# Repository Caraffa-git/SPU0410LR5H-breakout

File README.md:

# SPU0410LR5H-breakout

Simple SPU0410LR5H breakout board with an amplifier and a high-pass filter.

The panelized version is sized 35x75 mm and contains 4 boards.

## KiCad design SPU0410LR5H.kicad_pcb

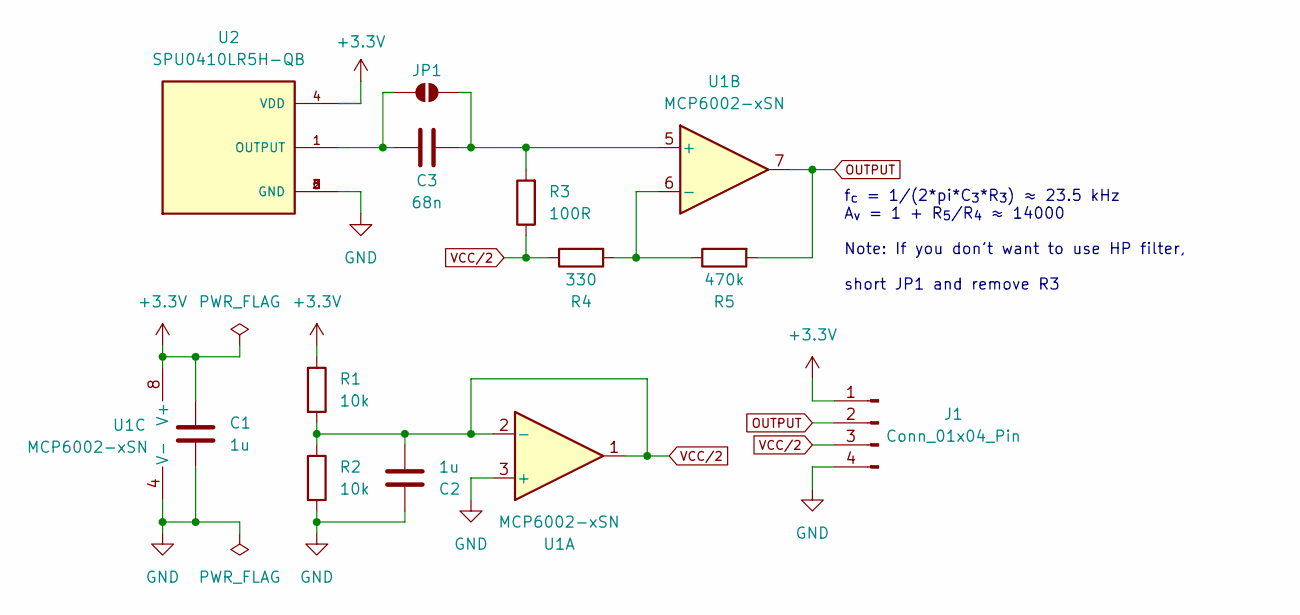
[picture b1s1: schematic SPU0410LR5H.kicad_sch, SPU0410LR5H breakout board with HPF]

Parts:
C1, C2: 1u; C_0805_2012Metric
C3: 68n; C_0805_2012Metric
J1: Conn_01x04_Pin; PinSocket_1x04_P2.54mm_Vertical
JP1: SolderJumper_2_Open; SolderJumper-2_P1.3mm_Open_RoundedPad1.0x1.5mm
R1, R2: 10k; R_0805_2012Metric
R3: 100R; R_0805_2012Metric
R4: 330; R_0805_2012Metric
R5: 470k; R_0805_2012Metric
U1: MCP6002-xSN; SOIC-8_3.9x4.9mm_P1.27mm
U2: SPU0410LR5H-QB; XDCR_SPU0410LR5H-QB; PARTREV H

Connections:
+3.3V: C1.1, J1.1, R1.1, U1.8 (V+), U2.4 (VDD)
GND: C1.2, C2.1, J1.4, R2.2, U1.3 (+), U1.4 (V-), U2.2 (GND), U2.3 (GND), U2.5 (GND), U2.6 (GND)
unnamed: C3.2, JP1.1 (A), U2.1 (OUTPUT)
unnamed: C3.1, JP1.2 (B), R3.2, U1.5 (+)
unnamed: R4.2, R5.1, U1.6 (-)
OUTPUT: J1.2, R5.2, U1.7
VCC/2: C2.2, J1.3, R1.2, R2.1, R3.1, R4.1, U1.1, U1.2 (-)

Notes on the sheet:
f_{c} = 1/(2*pi*C_{3}*R_{3}) ≈ 23.5 kHz A_{v} = 1 + R_{5}/R_{4} ≈ 14000 Note: If you don't want to use HP filter, short JP1 and remove R3

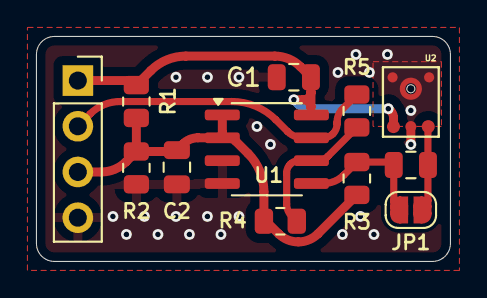
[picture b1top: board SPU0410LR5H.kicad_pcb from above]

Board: 2 copper layers, 23.0 x 12.5 mm, 16 parts (0 on the bottom side), 7 nets.

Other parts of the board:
kibuzzard-670AB1E7: G***; kibuzzard-670AB1E7
kibuzzard-670AB1F3: G***; kibuzzard-670AB1F3
kibuzzard-670AB20C: G***; kibuzzard-670AB20C
kibuzzard-670AB201: G***; kibuzzard-670AB201

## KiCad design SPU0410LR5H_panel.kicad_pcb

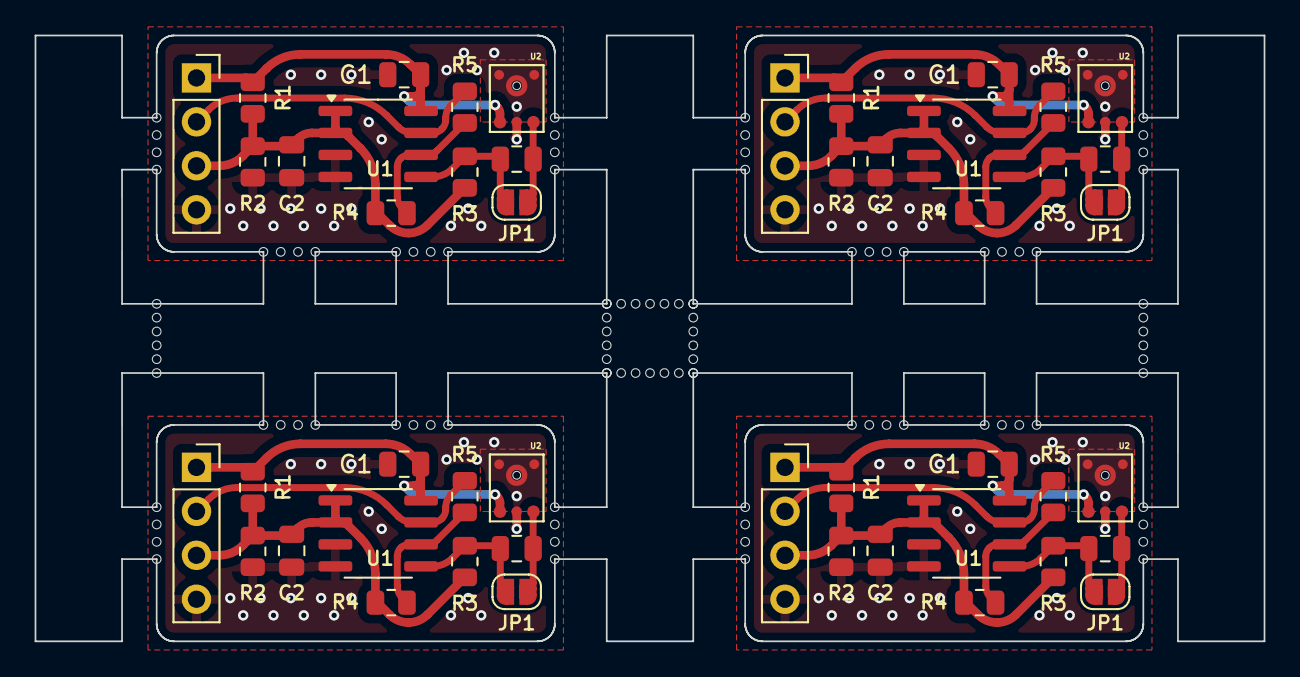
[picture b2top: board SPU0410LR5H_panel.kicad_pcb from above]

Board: 2 copper layers, 71.0 x 35.0 mm, 166 parts (0 on the bottom side), 28 nets.

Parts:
C1, C1#2, C1#3, C1#4, C2, C2#2, C2#3, C2#4: 1u; C_0805_2012Metric
C3, C3#2, C3#3, C3#4: 68n; C_0805_2012Metric
J1, J1#2, J1#3, J1#4: Conn_01x04_Pin; PinSocket_1x04_P2.54mm_Vertical
JP1, JP1#2, JP1#3, JP1#4: SolderJumper_2_Open; SolderJumper-2_P1.3mm_Open_RoundedPad1.0x1.5mm
KiKit_MB_1_1, KiKit_MB_1_2, KiKit_MB_1_3, KiKit_MB_1_4, KiKit_MB_2_1, KiKit_MB_2_2, KiKit_MB_2_3, KiKit_MB_2_4, KiKit_MB_3_1, KiKit_MB_3_2, KiKit_MB_3_3, KiKit_MB_3_4, KiKit_MB_4_1, KiKit_MB_4_2, KiKit_MB_4_3, KiKit_MB_4_4, KiKit_MB_5_1, KiKit_MB_5_2, KiKit_MB_5_3, KiKit_MB_5_4, KiKit_MB_6_1, KiKit_MB_6_2, KiKit_MB_6_3, KiKit_MB_6_4, KiKit_MB_7_1, KiKit_MB_7_2, KiKit_MB_7_3, KiKit_MB_7_4, KiKit_MB_8_1, KiKit_MB_8_2, KiKit_MB_8_3, KiKit_MB_8_4, KiKit_MB_9_1, KiKit_MB_9_2, KiKit_MB_9_3, KiKit_MB_9_4, KiKit_MB_10_1, KiKit_MB_10_2, KiKit_MB_10_3, KiKit_MB_10_4, KiKit_MB_11_1, KiKit_MB_11_2, KiKit_MB_11_3, KiKit_MB_11_4, KiKit_MB_12_1, KiKit_MB_12_2, KiKit_MB_12_3, KiKit_MB_12_4, KiKit_MB_13_1, KiKit_MB_13_2, KiKit_MB_13_3, KiKit_MB_13_4, KiKit_MB_14_1, KiKit_MB_14_2, KiKit_MB_14_3, KiKit_MB_14_4, KiKit_MB_15_1, KiKit_MB_15_2, KiKit_MB_15_3, KiKit_MB_15_4, KiKit_MB_16_1, KiKit_MB_16_2, KiKit_MB_16_3, KiKit_MB_16_4, KiKit_MB_17_1, KiKit_MB_17_2, KiKit_MB_17_3, KiKit_MB_17_4, KiKit_MB_17_5, KiKit_MB_17_6, KiKit_MB_18_1, KiKit_MB_18_2, KiKit_MB_18_3, KiKit_MB_18_4, KiKit_MB_18_5, KiKit_MB_18_6, KiKit_MB_19_1, KiKit_MB_19_2, KiKit_MB_19_3, KiKit_MB_19_4, KiKit_MB_19_5, KiKit_MB_19_6, KiKit_MB_20_1, KiKit_MB_20_2, KiKit_MB_20_3, KiKit_MB_20_4, KiKit_MB_20_5, KiKit_MB_20_6, KiKit_MB_21_1, KiKit_MB_21_2, KiKit_MB_21_3, KiKit_MB_21_4, KiKit_MB_21_5, KiKit_MB_21_6, KiKit_MB_21_7, KiKit_MB_22_1, KiKit_MB_22_2, KiKit_MB_22_3, KiKit_MB_22_4, KiKit_MB_22_5, KiKit_MB_22_6, KiKit_MB_22_7: NPTH
R1, R1#2, R1#3, R1#4, R2, R2#2, R2#3, R2#4: 10k; R_0805_2012Metric
R3, R3#2, R3#3, R3#4: 100R; R_0805_2012Metric
R4, R4#2, R4#3, R4#4: 330; R_0805_2012Metric
R5, R5#2, R5#3, R5#4: 470k; R_0805_2012Metric
U1, U1#2, U1#3, U1#4: MCP6002-xSN; SOIC-8_3.9x4.9mm_P1.27mm
U2, U2#2, U2#3, U2#4: SPU0410LR5H-QB; XDCR_SPU0410LR5H-QB
kibuzzard-670AB1E7, kibuzzard-670AB1E7#2, kibuzzard-670AB1E7#3, kibuzzard-670AB1E7#4: G***; kibuzzard-670AB1E7
kibuzzard-670AB1F3, kibuzzard-670AB1F3#2, kibuzzard-670AB1F3#3, kibuzzard-670AB1F3#4: G***; kibuzzard-670AB1F3
kibuzzard-670AB20C, kibuzzard-670AB20C#2, kibuzzard-670AB20C#3, kibuzzard-670AB20C#4: G***; kibuzzard-670AB20C
kibuzzard-670AB201, kibuzzard-670AB201#2, kibuzzard-670AB201#3, kibuzzard-670AB201#4: G***; kibuzzard-670AB201

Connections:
Board_0-+3.3V: C1#3.1, J1#3.1, R1.1, U1#3.8 (V+), U2#2.4 (VDD)
Board_0-GND: C1#3.2, C2#3.1, J1#3.4, R2#4.2, U1#3.3 (+), U1#3.4 (V-), U2#2.2 (GND), U2#2.3 (GND), U2#2.5 (GND), U2#2.6 (GND)
Board_0-Net-(JP1-A): C3#3.2, JP1#2.1 (A), U2#2.1 (OUTPUT)
Board_0-Net-(JP1-B): C3#3.1, JP1#2.2 (B), R3.2, U1#3.5 (+)
Board_0-Net-(U1B--): R4#3.2, R5#3.1, U1#3.6 (-)
Board_0-OUTPUT: J1#3.2, R5#3.2, U1#3.7
Board_0-VCC/2: C2#3.2, J1#3.3, R1.2, R2#4.1, R3.1, R4#3.1, U1#3.1, U1#3.2 (-)
Board_1-+3.3V: C1#4.1, J1#4.1, R1#2.1, U1#4.8 (V+), U2#3.4 (VDD)
Board_1-GND: C1#4.2, C2#2.1, J1#4.4, R2#2.2, U1#4.3 (+), U1#4.4 (V-), U2#3.2 (GND), U2#3.3 (GND), U2#3.5 (GND), U2#3.6 (GND)
Board_1-Net-(JP1-A): C3.2, JP1#4.1 (A), U2#3.1 (OUTPUT)
Board_1-Net-(JP1-B): C3.1, JP1#4.2 (B), R3#4.2, U1#4.5 (+)
Board_1-Net-(U1B--): R4#2.2, R5#2.1, U1#4.6 (-)
Board_1-OUTPUT: J1#4.2, R5#2.2, U1#4.7
Board_1-VCC/2: C2#2.2, J1#4.3, R1#2.2, R2#2.1, R3#4.1, R4#2.1, U1#4.1, U1#4.2 (-)
Board_2-+3.3V: C1.1, J1#2.1, R1#3.1, U1.8 (V+), U2.4 (VDD)
Board_2-GND: C1.2, C2.1, J1#2.4, R2#3.2, U1.3 (+), U1.4 (V-), U2.2 (GND), U2.3 (GND), U2.5 (GND), U2.6 (GND)
Board_2-Net-(JP1-A): C3#2.2, JP1.1 (A), U2.1 (OUTPUT)
Board_2-Net-(JP1-B): C3#2.1, JP1.2 (B), R3#3.2, U1.5 (+)
Board_2-Net-(U1B--): R4#4.2, R5#4.1, U1.6 (-)
Board_2-OUTPUT: J1#2.2, R5#4.2, U1.7
Board_2-VCC/2: C2.2, J1#2.3, R1#3.2, R2#3.1, R3#3.1, R4#4.1, U1.1, U1.2 (-)
Board_3-+3.3V: C1#2.1, J1.1, R1#4.1, U1#2.8 (V+), U2#4.4 (VDD)
Board_3-GND: C1#2.2, C2#4.1, J1.4, R2.2, U1#2.3 (+), U1#2.4 (V-), U2#4.2 (GND), U2#4.3 (GND), U2#4.5 (GND), U2#4.6 (GND)
Board_3-Net-(JP1-A): C3#4.2, JP1#3.1 (A), U2#4.1 (OUTPUT)
Board_3-Net-(JP1-B): C3#4.1, JP1#3.2 (B), R3#2.2, U1#2.5 (+)
Board_3-Net-(U1B--): R4.2, R5.1, U1#2.6 (-)
Board_3-OUTPUT: J1.2, R5.2, U1#2.7
Board_3-VCC/2: C2#4.2, J1.3, R1#4.2, R2.1, R3#2.1, R4.1, U1#2.1, U1#2.2 (-)

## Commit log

2025-02-18 update silkscreen
2025-02-18 panel fix
2025-02-18 silkscreen fix
